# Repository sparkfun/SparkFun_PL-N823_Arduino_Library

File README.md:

SparkFun Qwiic PL-N823 IR Breakout
==================================

[*SparkFun Qwiic IR Breakout (SPX-15804)*](https://www.sparkfun.com/products/15804)

Repository Contents
-------------------

* **/Hardware** - Current Eagle files for product
* **/examples** - Measurement and peak-detection examples for the PL-N823

Documentation
-------------
* **[Installing an Arduino Library Guide](https://learn.sparkfun.com/tutorials/installing-an-arduino-library)** - Basic information on how to install an Arduino library.

License Information
-------------------

This product is _**open source**_!

Please review the LICENSE.md file for license information.

If you have any questions or concerns on licensing, please contact technical support on our [SparkFun forums](https://forum.sparkfun.com/viewforum.php?f=152).

Distributed as-is; no warranty is given.

- Your friends at SparkFun.

_<COLLABORATION CREDIT>_

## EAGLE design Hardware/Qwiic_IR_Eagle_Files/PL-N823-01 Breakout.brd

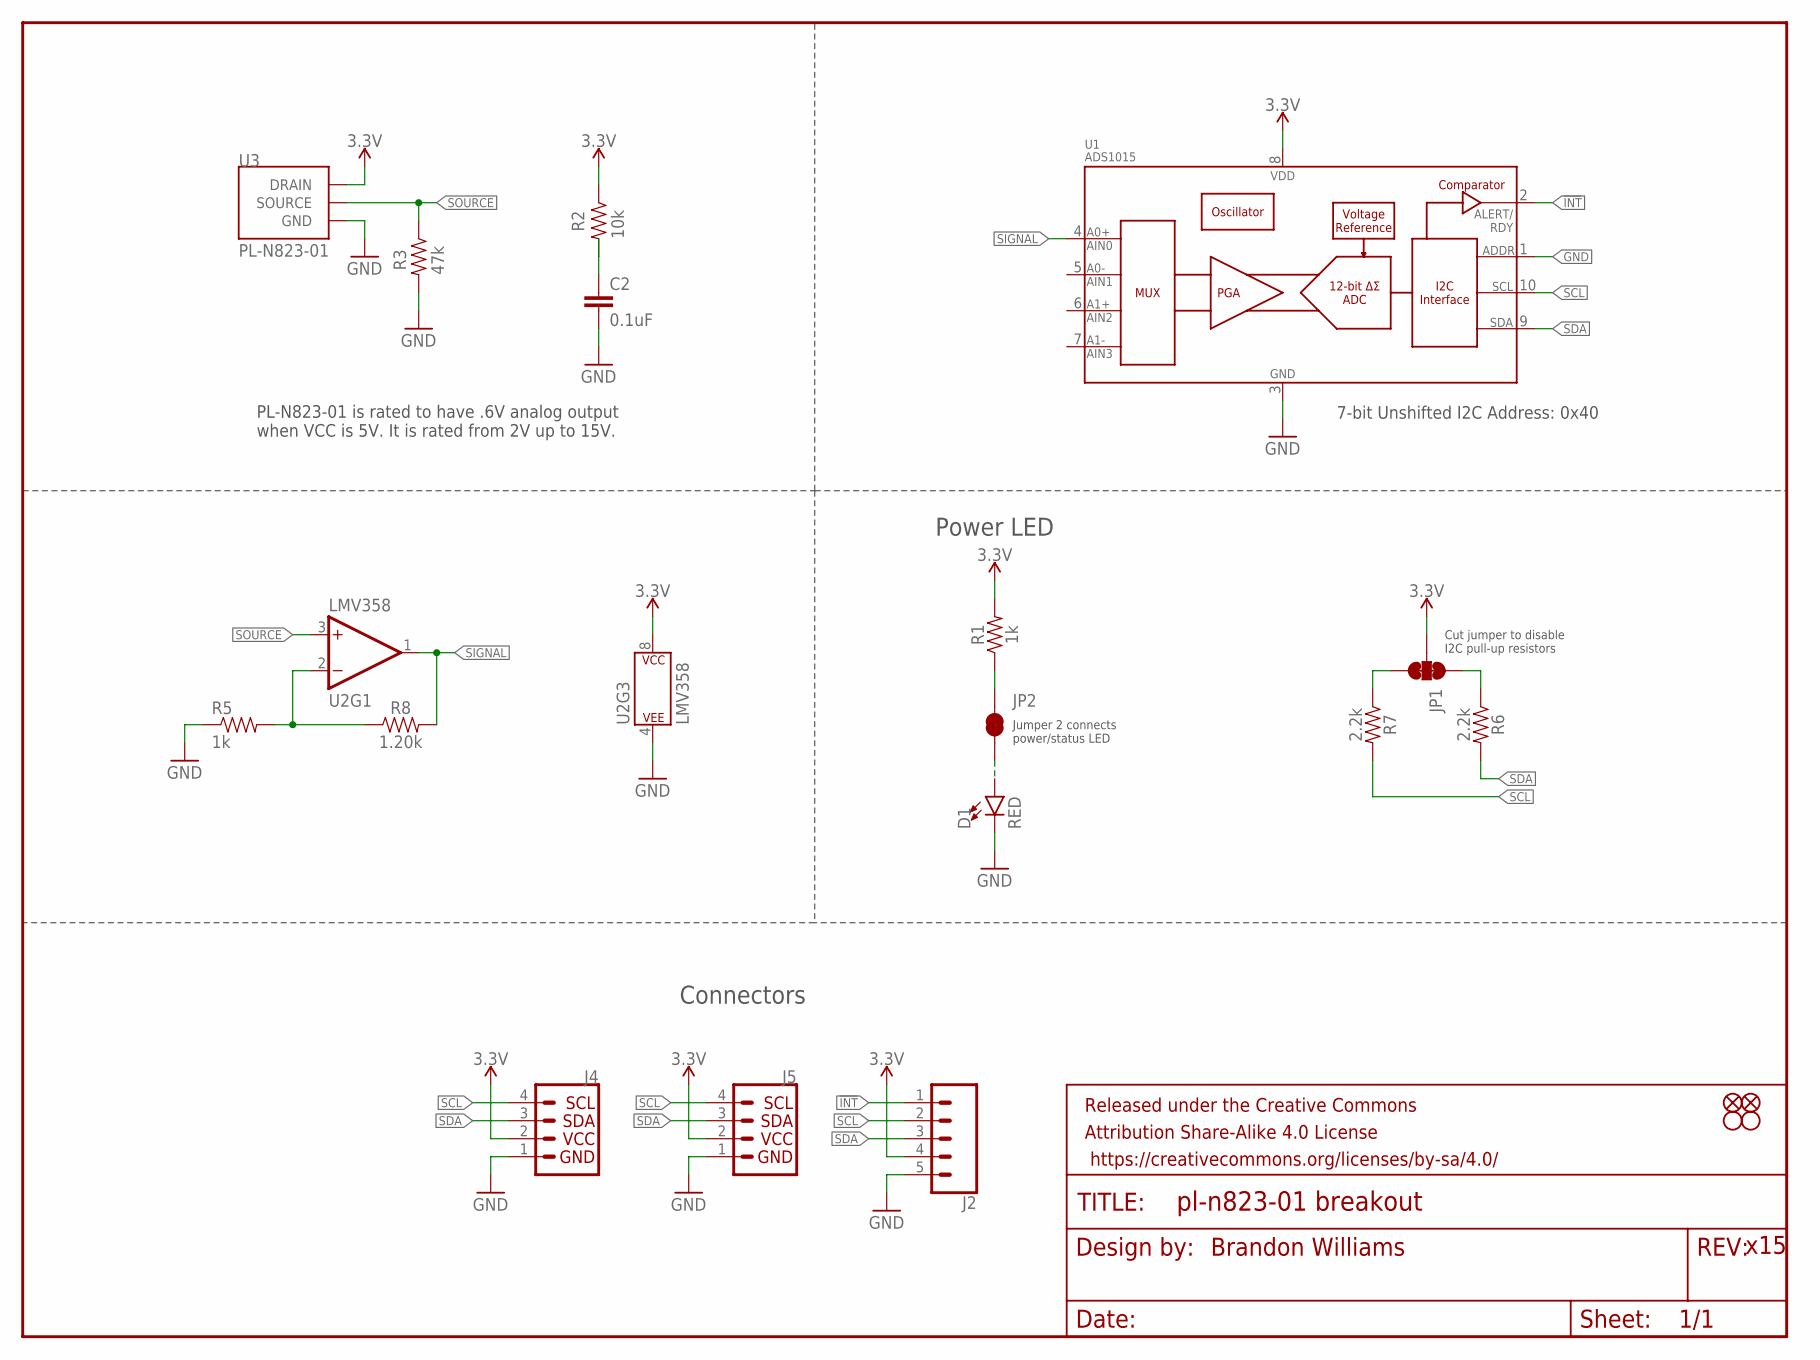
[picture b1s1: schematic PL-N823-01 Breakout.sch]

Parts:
C2: 0.1uF; 0603
D1: RED; LED-0603
FD1, FD2: FIDUCIALUFIDUCIAL; FIDUCIAL-MICRO
FRAME1: FRAME-LETTERNO_PACKAGE; DUMMY
H1, H2: STAND-OFFTIGHT; STAND-OFF-TIGHT
J2: CONN_05NO_SILK; 1X05_NO_SILK
J4, J5: QWIIC_CONNECTORJS-1MM; JST04_1MM_RA
JP1: JUMPER-SMT_3_2-NC_TRACE_SILK; SMT-JUMPER_3_2-NC_TRACE_SILK
JP2: JUMPER-SMT_2_NC_TRACE_SILK; SMT-JUMPER_2_NC_TRACE_SILK
R1, R5: 1k; 0603
R2: 10k; 0603
R3: 47k; 0603
R6, R7: 2.2k; 0603
R8: 1.20k; 0603
U1: ADS1015; MSOP10
U2: LMV358; SO08
U3: PL-N823-01

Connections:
3.3V: J2.4, J4.2, J5.2, JP1.2, R1.2, R2.1, U1.8 (VDD), U2.8 (P$V+), U3.DRAIN
!INT: J2.1, U1.2 (ALERT/RDY)
GND: C2.2, D1.C, J2.5, J4.1, J5.1, R3.2, R5.1, U1.1 (ADDR), U1.3 (VSS), U2.4 (P$V-), U3.GND@1 (GND), U3.GND@2 (GND)
unnamed: R5.2, R8.1, U2.2 (-IN)
unnamed: C2.1, R2.2
unnamed: JP2.1, R1.1
unnamed: JP1.3, R7.1
unnamed: JP1.1, R6.1
unnamed: D1.A, JP2.2
SCL: J2.2, J4.4, J5.4, R7.2, U1.10 (SCL)
SDA: J2.3, J4.3, J5.3, R6.2, U1.9 (SDA)
SIGNAL: R8.2, U1.4 (AIN0), U2.1 (OUT)
SOURCE: R3.1, U2.3 (+IN), U3.SOURCE

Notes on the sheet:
Brandon Williams
x15
7-bit Unshifted I2C Address: 0x40
Power LED
Jumper 2 connects power/status LED
Cut jumper to disable I2C pull-up resistors
PL-N823-01 is rated to have .6V analog output when VCC is 5V. It is rated from 2V up to 15V.
Connectors

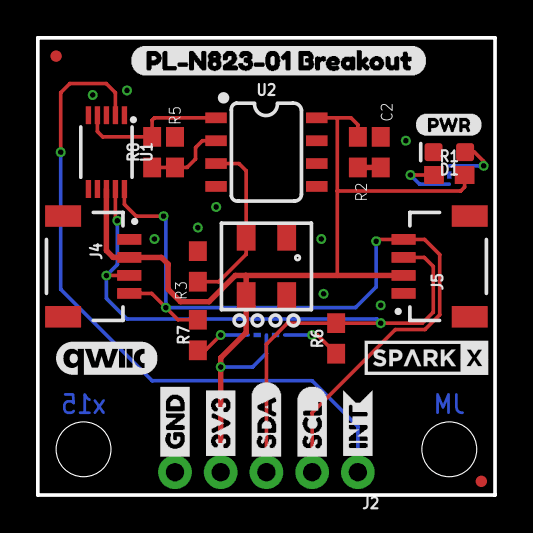
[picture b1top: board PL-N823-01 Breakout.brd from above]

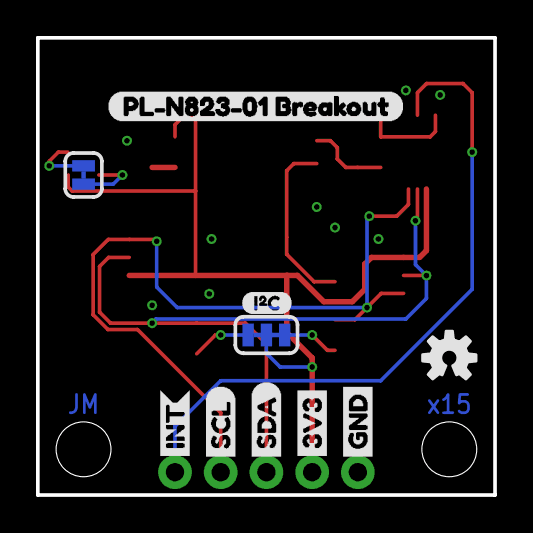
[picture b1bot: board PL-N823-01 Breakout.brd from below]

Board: 4 copper layers, 25.4 x 25.4 mm, 39 parts (10 on the bottom side), 13 nets.

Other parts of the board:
U$1: QWIIC_COPYRIGHT_SMALL
U$2, U$13: SDA-[)
U$3, U$21: INT0
U$4, U$8: PL#N823#01_BREAKOUT0
U$5: I_SUPER2_C-()-03
U$7: OSHW-LOGO-S
U$9: PWR-()-03
U$10: SPARKX-SMALL
U$12, U$14: SCL-[)
U$15, U$16: 3V3-04
U$17, U$18: GND-04

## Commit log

2019-09-18 Upload Eagle files and sensor library
2019-09-19 Add basic reading and calibrated reading sketches
2019-10-23 Updating examples to work with ADS library
    Superficial board changes
2019-10-23 Create PL-N823-01 Breakout.b#2
2019-10-30 Updated calibrated reading
2019-10-30 Fixing examples
2019-11-18 Comment clean-up and example 2 rename.
2019-11-18 Remove hardware repo

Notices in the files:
parts and their libraries:
SparkFun-IC-Conversion: Licensing: Creative Commons ShareAlike 4.0 International - https://creativecommons.org/licenses/by-sa/4.0
SparkFun-Aesthetics: Released under the Creative Commons Attribution Share-Alike 4.0 License
SparkFun-Aesthetics: https://creativecommons.org/licenses/by-sa/4.0
